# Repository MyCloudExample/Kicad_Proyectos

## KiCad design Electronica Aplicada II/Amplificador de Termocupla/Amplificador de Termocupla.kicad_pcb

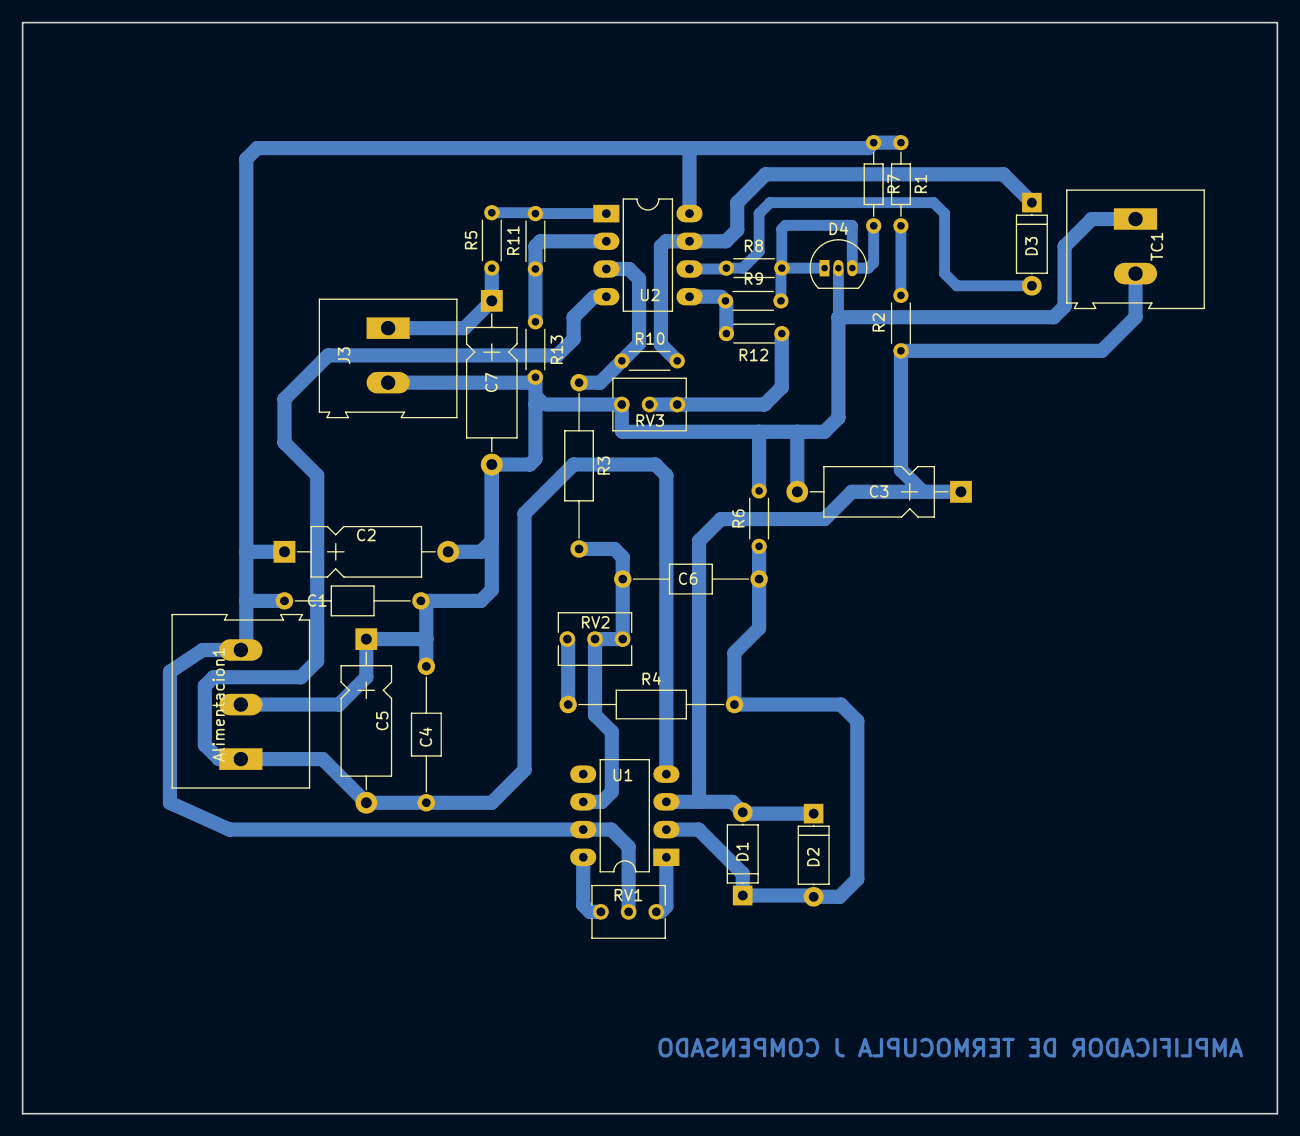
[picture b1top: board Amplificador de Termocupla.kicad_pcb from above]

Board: 2 copper layers, 115.0 x 100.0 mm, 32 parts (0 on the bottom side), 19 nets.

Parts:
Alimentacion1: -15 GND +15; TerminalBlock_Altech_AK300-3_P5.00mm
C1, C4, C6: 0.1uF; C_Axial_L3.8mm_D2.6mm_P12.50mm_Horizontal
C2, C5: 100uF; CP_Axial_L10.0mm_D4.5mm_P15.00mm_Horizontal
C3, C7: 1uF; CP_Axial_L10.0mm_D4.5mm_P15.00mm_Horizontal
D1, D2, D3: D_A-405_P7.62mm_Horizontal
D4: TL431LP; TO-92_Inline_Narrow_Oval
J3: Sensor_V_Out; TerminalBlock_Altech_AK300-2_P5.00mm
R1: 1M; R_Axial_DIN0204_L3.6mm_D1.6mm_P7.62mm_Horizontal
R2, R5, R6: 1K; R_Axial_DIN0204_L3.6mm_D1.6mm_P5.08mm_Horizontal
R3: 10K; R_Axial_DIN0207_L6.3mm_D2.5mm_P15.24mm_Horizontal
R4: 39K; R_Axial_DIN0207_L6.3mm_D2.5mm_P15.24mm_Horizontal
R7: R; R_Axial_DIN0204_L3.6mm_D1.6mm_P7.62mm_Horizontal
R8, R9: 18K; R_Axial_DIN0204_L3.6mm_D1.6mm_P5.08mm_Horizontal
R10, R13: 10K; R_Axial_DIN0204_L3.6mm_D1.6mm_P5.08mm_Horizontal
R11: 75K; R_Axial_DIN0204_L3.6mm_D1.6mm_P5.08mm_Horizontal
R12: 4K7; R_Axial_DIN0204_L3.6mm_D1.6mm_P5.08mm_Horizontal
RV1: 20K; Potentiometer_Trimmer_Vishay_T73XW_Vertical
RV2: 10K; Potentiometer_Trimmer_Vishay_T73XW_Vertical
RV3: 1K; Potentiometer_Trimmer_Vishay_T73XW_Vertical
TC1: Termocupla J; TerminalBlock_Altech_AK300-2_P5.00mm
U1: OP07; DIP-8_W7.62mm_LongPads
U2: LM358; DIP-8_W7.62mm_LongPads

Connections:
Earth: Alimentacion1.2, C1.2, C2.2, C3.2, C4.1, C5.1, C7.2, D4.2, J3.2, R6.2, R13.1, RV3.3, TC1.1
unnamed: C3.1, D1.2, D2.1, R2.2, TC1.2, U1.3
unnamed: C6.1, R3.2, RV2.1, RV2.2, U1.6
unnamed: C6.2, D1.1, D2.2, R4.2, R6.1, U1.2
unnamed: C7.1, J3.1, R5.1
unnamed: D3.1, R10.1, U2.7
unnamed: D3.2, R8.1, U2.6
unnamed: D4.1, D4.3, R7.2, R8.2, R9.1
unnamed: R1.2, R2.1
unnamed: R4.1, RV2.3
unnamed: R3.1, R10.2, U2.3
unnamed: R5.2, R11.1, U2.1
unnamed: R11.2, R13.2, U2.2
unnamed: R9.2, R12.1, U2.5
unnamed: R12.2, RV3.1, RV3.2
unnamed: RV1.1, U1.8
unnamed: RV1.3, U1.1
VDD: Alimentacion1.3, C1.1, C2.1, R1.1, R7.1, RV1.2, U1.7, U2.8
VEE: Alimentacion1.1, C4.2, C5.2, U1.4, U2.4

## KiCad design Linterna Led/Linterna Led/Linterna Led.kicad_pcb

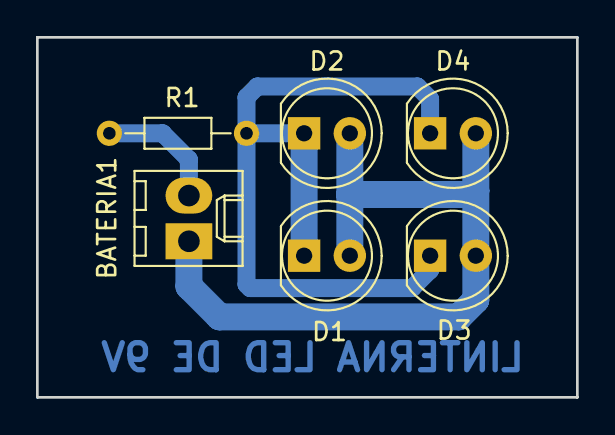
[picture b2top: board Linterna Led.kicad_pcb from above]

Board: 2 copper layers, 30.0 x 20.0 mm, 6 parts (0 on the bottom side), 3 nets.

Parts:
BATERIA1: Molex_KK-6410-02_02x2.54mm_Straight
D1, D2, D3, D4: LED_D5.0mm_FlatTop
R1: 220; R_Axial_DIN0204_L3.6mm_D1.6mm_P7.62mm_Horizontal

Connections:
unnamed: BATERIA1.1, D1.2, D2.2, D3.2, D4.2
unnamed: BATERIA1.2, R1.2
unnamed: D1.1, D2.1, D3.1, D4.1, R1.1

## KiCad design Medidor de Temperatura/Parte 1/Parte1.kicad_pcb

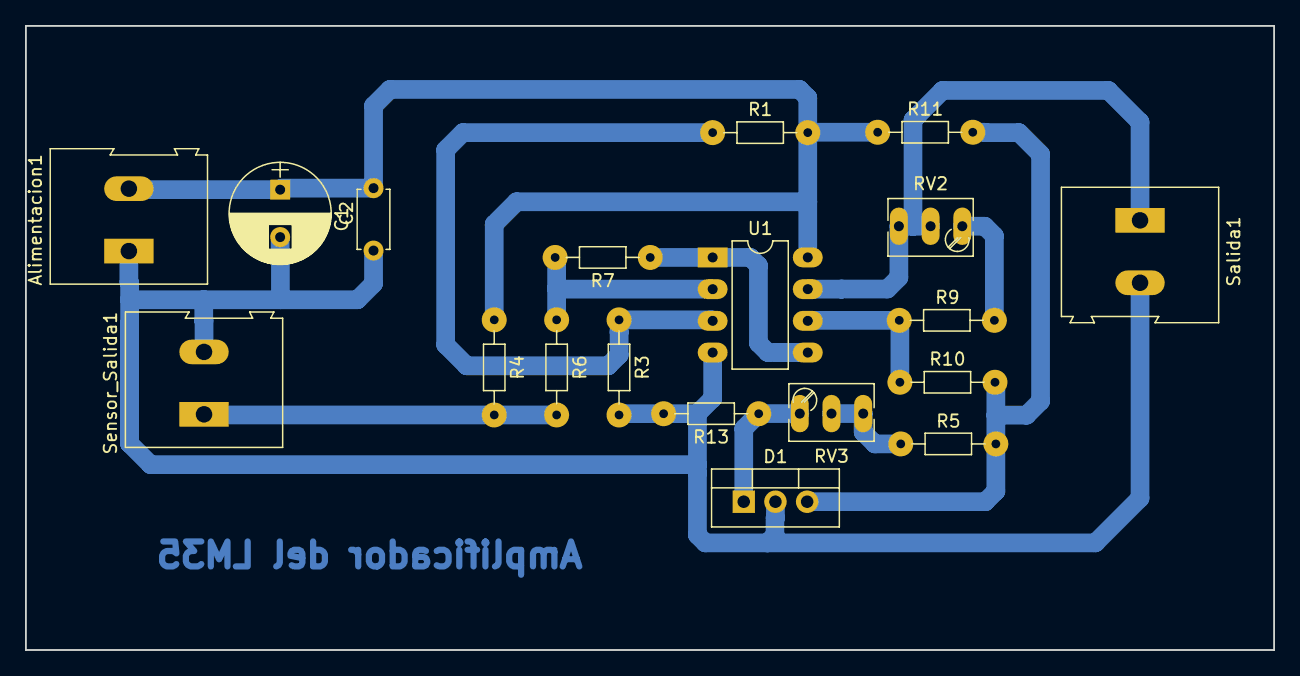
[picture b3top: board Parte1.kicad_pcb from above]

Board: 2 copper layers, 100.0 x 50.0 mm, 19 parts (0 on the bottom side), 12 nets.

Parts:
Alimentacion1: TerminalBlock_Altech_AK300-2_P5.00mm
C1: C; C_Disc_D4.7mm_W2.5mm_P5.00mm
C2: CP; CP_Radial_D8.0mm_P3.80mm
D1: TL431P; TO-220-3_Vertical
R1, R3, R6, R7, R10: 10k; R_Axial_DIN0204_L3.6mm_D1.6mm_P7.62mm_Horizontal
R4: 250; R_Axial_DIN0204_L3.6mm_D1.6mm_P7.62mm_Horizontal
R5: 1k5; R_Axial_DIN0204_L3.6mm_D1.6mm_P7.62mm_Horizontal
R9: 1k8; R_Axial_DIN0204_L3.6mm_D1.6mm_P7.62mm_Horizontal
R11: 4k7; R_Axial_DIN0204_L3.6mm_D1.6mm_P7.62mm_Horizontal
R13: 2k2; R_Axial_DIN0204_L3.6mm_D1.6mm_P7.62mm_Horizontal
RV2, RV3: 1k; Potentiometer_Trimmer_Bourns_3266Y
Salida1: TerminalBlock_Altech_AK300-2_P5.00mm
Sensor_Salida1: TerminalBlock_Altech_AK300-2_P5.00mm
U1: LM358; DIP-8_W7.62mm_LongPads

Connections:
GNDREF: Alimentacion1.1, C1.1, C2.2, D1.2, R3.2, R13.2, Salida1.2, Sensor_Salida1.2, U1.4
unnamed: D1.1, R13.1, RV3.1
unnamed: D1.3, R5.1, R10.2, R11.2
unnamed: R1.1, R3.1, U1.3
unnamed: R4.2, R6.2, Sensor_Salida1.1
unnamed: R5.2, RV3.2, RV3.3
unnamed: R6.1, R7.2, U1.2
unnamed: R7.1, U1.1, U1.5
unnamed: R9.1, RV2.1
unnamed: R9.2, R10.1, U1.6
unnamed: RV2.2, RV2.3, Salida1.1, U1.7
VDD: Alimentacion1.2, C1.2, C2.1, R1.2, R4.1, R11.1, U1.8

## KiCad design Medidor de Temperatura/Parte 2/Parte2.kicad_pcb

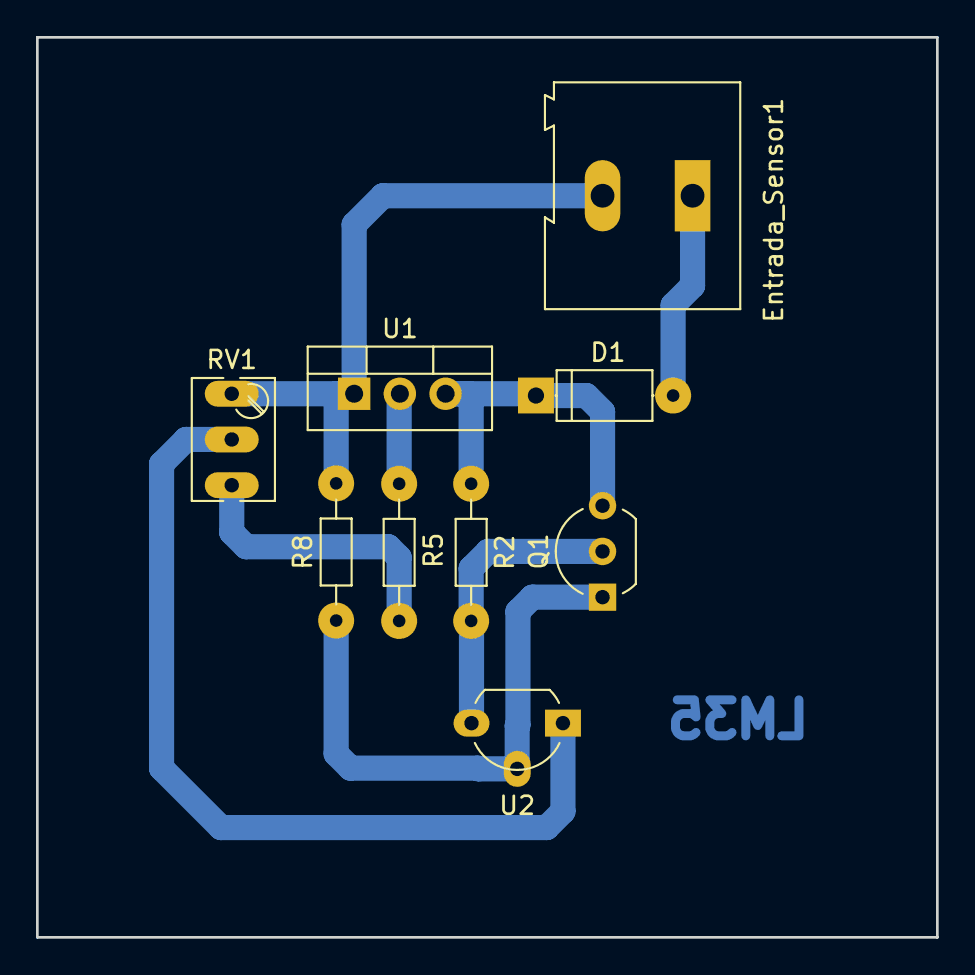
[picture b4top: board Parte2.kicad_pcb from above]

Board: 2 copper layers, 50.0 x 50.0 mm, 9 parts (0 on the bottom side), 8 nets.

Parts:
D1: 1N5819; D_A-405_P7.62mm_Horizontal
Entrada_Sensor1: TerminalBlock_Altech_AK300-2_P5.00mm
Q1: BC557; TO-92_Inline_Wide
R2: 4k7; R_Axial_DIN0204_L3.6mm_D1.6mm_P7.62mm_Horizontal
R5: 560; R_Axial_DIN0204_L3.6mm_D1.6mm_P7.62mm_Horizontal
R8: 62,5; R_Axial_DIN0204_L3.6mm_D1.6mm_P7.62mm_Horizontal
RV1: 100; Potentiometer_Trimmer_Bourns_3266Y
U1: LM317L_TO92; TO-220-3_Vertical
U2: LM35-LP; TO-92_Molded_Wide_Oval

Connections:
GNDREF: Entrada_Sensor1.2, R8.2, RV1.1, U1.1
unnamed: D1.1, Q1.3, R2.1, U1.3
unnamed: D1.2, Entrada_Sensor1.1
unnamed: Q1.1, R8.1, U2.2
unnamed: Q1.2, R2.2, U2.3
unnamed: R5.1, U1.2
unnamed: R5.2, RV1.3
unnamed: RV1.2, U2.1

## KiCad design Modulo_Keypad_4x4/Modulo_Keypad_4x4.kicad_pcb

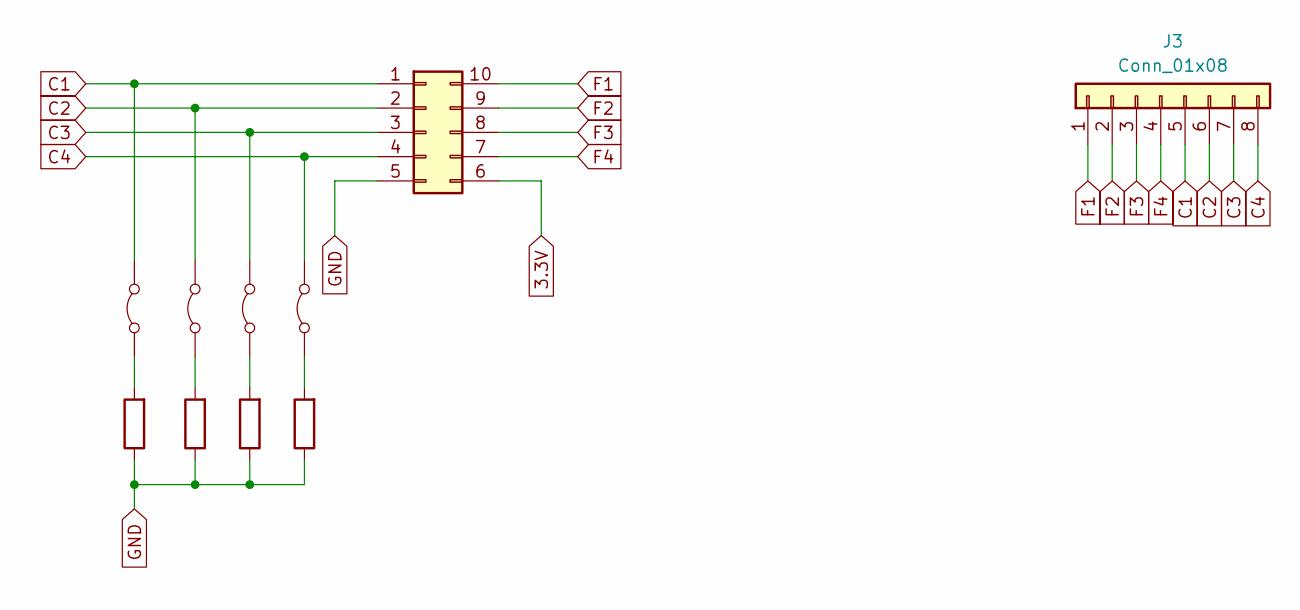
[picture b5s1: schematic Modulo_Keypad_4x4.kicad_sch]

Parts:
J2: Conn_02x05_Counter_Clockwise; Molex_Micro-Fit_3.0_43045-1012_2x05_P3.00mm_Vertical
J3: Conn_01x08; TerminalBlock_Phoenix_MKDS-1,5-8-5.08_1x08_P5.08mm_Horizont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
JP5, JP6, JP7, JP8: Jumper_2_Bridged; PinHeader_1x02_P2.00mm_Vertical
R5, R6, R7, R8: 10k; R_Axial_DIN0204_L3.6mm_D1.6mm_P7.62mm_Horizontal

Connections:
3.3V: J2.6
C1: J2.1, J3.5, JP8.2 (B)
C2: J2.2, J3.6, JP7.2 (B)
C3: J2.3, J3.7, JP6.2 (B)
C4: J2.4, J3.8, JP5.2 (B)
F1: J2.10, J3.1
F2: J2.9, J3.2
F3: J2.8, J3.3
F4: J2.7, J3.4
GND: J2.5, R5.1, R6.1, R7.1, R8.1
unnamed: JP5.1 (A), R5.2
unnamed: JP6.1 (A), R6.2
unnamed: JP7.1 (A), R7.2
unnamed: JP8.1 (A), R8.2

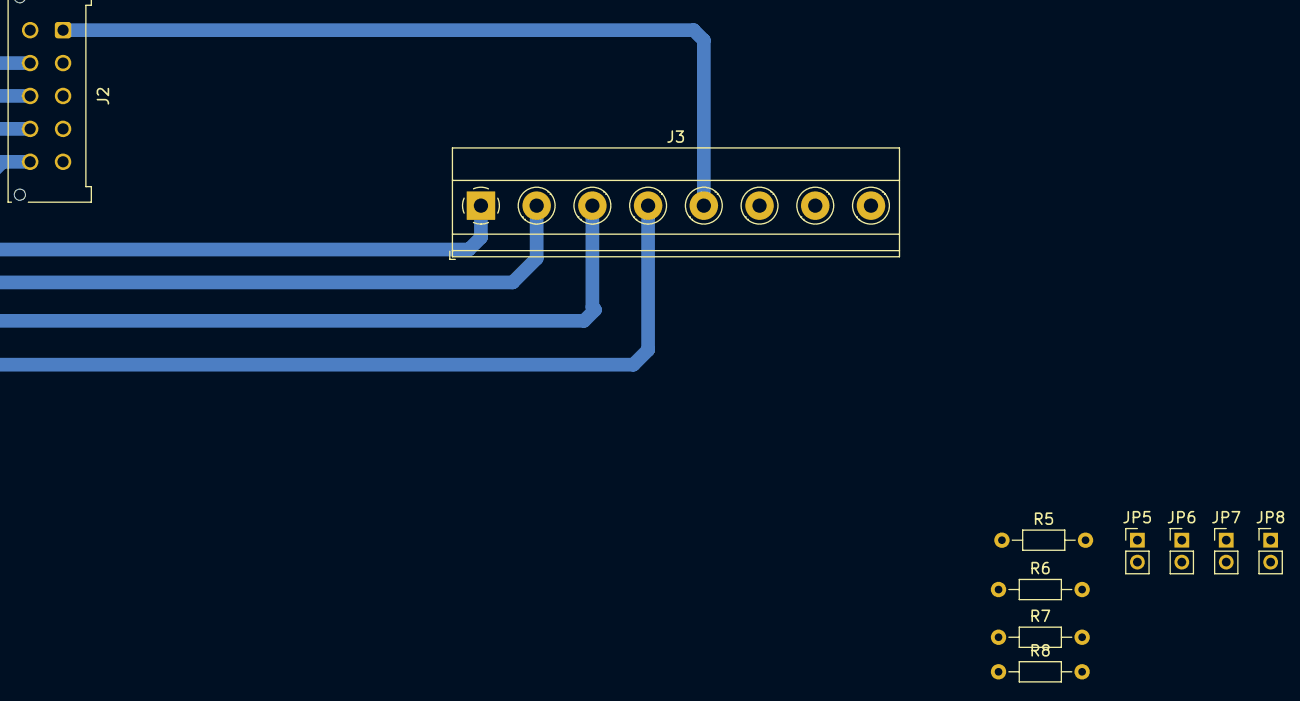
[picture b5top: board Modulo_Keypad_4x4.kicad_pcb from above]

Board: 2 copper layers, 10 parts (0 on the bottom side), 13 nets.

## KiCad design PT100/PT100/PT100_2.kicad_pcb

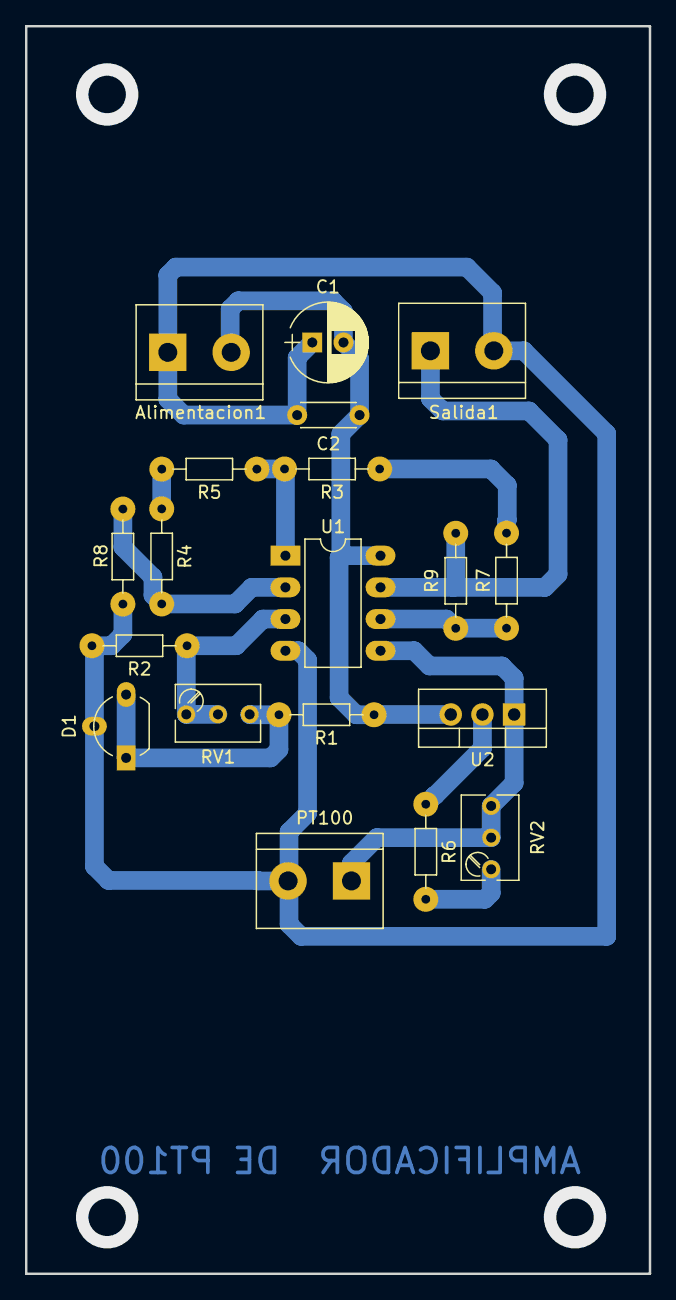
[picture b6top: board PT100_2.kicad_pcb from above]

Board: 2 copper layers, 50.0 x 100.0 mm, 19 parts (0 on the bottom side), 13 nets.

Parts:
Alimentacion1: TerminalBlock_bornier-2_P5.08mm
C1: 100uF; CP_Radial_D6.3mm_P2.50mm
C2: 0,1uF; C_Disc_D4.3mm_W1.9mm_P5.00mm
D1: TL431LP; TO-92_Molded_Wide_Oval
PT100: TerminalBlock_bornier-2_P5.08mm
R1: 4k7; R_Axial_DIN0204_L3.6mm_D1.6mm_P7.62mm_Horizontal
R2: 470; R_Axial_DIN0204_L3.6mm_D1.6mm_P7.62mm_Horizontal
R3, R4, R5, R7: 1k2; R_Axial_DIN0204_L3.6mm_D1.6mm_P7.62mm_Horizontal
R6: 180; R_Axial_DIN0204_L3.6mm_D1.6mm_P7.62mm_Horizontal
R8, R9: 10k; R_Axial_DIN0204_L3.6mm_D1.6mm_P7.62mm_Horizontal
RV1: 1k5; Potentiometer_Trimmer_Bourns_3266Y
RV2: 100; Potentiometer_Trimmer_Bourns_3266Y
Salida1: TerminalBlock_bornier-2_P5.08mm
U1: LM358; DIP-8_W7.62mm_LongPads
U2: LM317_3PinPackage; TO-220-3_Vertical

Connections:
GNDREF: Alimentacion1.1, C1.1, C2.1, D1.2, PT100.2, R2.2, R8.2, Salida1.2, U1.4
unnamed: D1.1, D1.3, R1.2, RV1.3
unnamed: PT100.1, RV2.2, RV2.3, U1.5, U2.1
unnamed: R2.1, RV1.1, RV1.2, U1.3
unnamed: R3.1, R7.2
unnamed: R3.2, R5.1, U1.1
unnamed: R4.1, R5.2
unnamed: R4.2, R8.1, U1.2
unnamed: R6.1, U2.2
unnamed: R6.2, RV2.1
unnamed: R7.1, R9.2, U1.6
unnamed: R9.1, Salida1.1, U1.7
VDD: Alimentacion1.2, C1.2, C2.2, R1.1, U1.8, U2.3
